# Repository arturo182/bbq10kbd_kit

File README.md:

# Untested

While the keyboard footprint and symbol are tested, the rest of the board is not, approach with caution.

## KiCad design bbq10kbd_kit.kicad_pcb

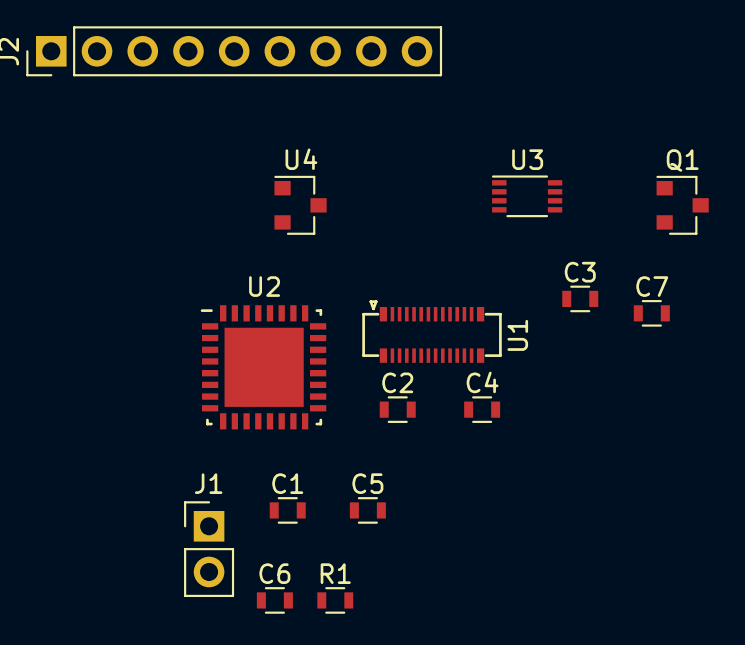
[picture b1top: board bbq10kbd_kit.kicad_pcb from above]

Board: 2 copper layers, 15 parts (0 on the bottom side), 16 nets, no tracks yet.

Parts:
C1: 4.7uF; R_0603
C2, C3, C4: 0.1uF; R_0603
C5: 10nF; R_0603
C6, C7: 1uF; R_0603
J1: SWD; Pin_Header_Straight_1x02_Pitch2.54mm
J2: Conn_01x09; Pin_Header_Straight_1x09_Pitch2.54mm
Q1: BSS138; SOT-23
R1: 10K; R_0603
U1: BBQ10KBD; BM14B(0.8)-24DS-0.4V(53)
U2: EFM32ZG210; QFN-32_EP_6x6_Pitch0.65mm
U3: SN74LVC3G07DCUR; VSSOP-8_2.3x2mm_Pitch0.5mm
U4: MCP1700T-3302E; SOT-23

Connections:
+3V3: C1.1, C2.1, C3.1, C4.1, C5.1, J2.8, U1.2, U1.24, U1.26, U2.4, U2.11, U2.14, U2.15, U2.20, U2.28, U3.8, U4.2
/KBD_BL: Q1.1, R1.1
/KBD_MIC: J2.1, U1.3
/SPI_CS: U2.8, U3.5
/SPI_CS_IN: J2.3, U3.3
/SPI_MISO: J2.5, U2.5
/SPI_MOSI: U2.6, U3.2
/SPI_MOSI_IN: J2.4, U3.6
/SPI_SCK: U2.7, U3.7
/SPI_SCK_IN: J2.6, U3.1
/SWCLK: J1.1, U2.25
/SWDIO: J1.2, U2.26
GND: C1.2, C2.2, C3.2, C4.2, C5.2, C6.2, C7.1, J2.7, Q1.2, R1.2, U1.1, U1.4, U1.5, U1.11, U1.12, U1.13, U1.14, U1.15, U1.16, U1.28, U2.33, U3.4, U4.1
unnamed: C6.1, U2.21
unnamed: Q1.3, U1.23, U1.25
VDD: C7.2, J2.9, U2.9, U4.3

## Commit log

2018-01-10 Initial import
2018-01-13 Added readme
